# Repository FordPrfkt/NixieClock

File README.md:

# NixieClock
ESP12 based universal base board for nixie clocks and IN14-Tube board

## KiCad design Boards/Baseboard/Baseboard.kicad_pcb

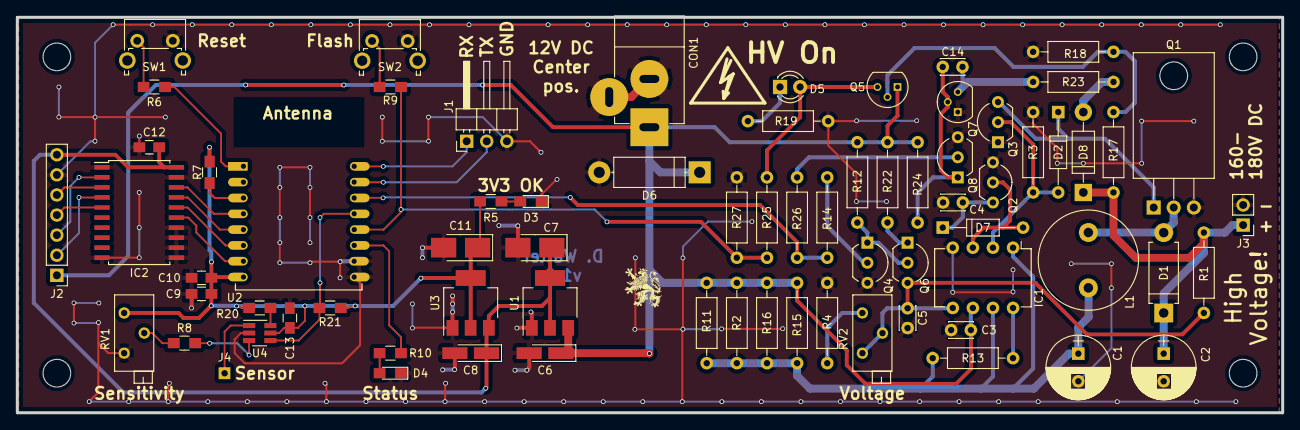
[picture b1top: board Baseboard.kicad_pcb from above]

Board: 2 copper layers, 160.0 x 50.0 mm, 73 parts (0 on the bottom side), 48 nets.

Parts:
C1: 220µF/25V; CP_Radial_D8.0mm_P3.50mm
C2: 2µ2 / 250V; CP_Radial_D8.0mm_P3.50mm
C3: 100nF; C_Disc_D3.0mm_W2.0mm_P2.50mm
C4, C14: 1.5nF; C_Disc_D3.0mm_W2.0mm_P2.50mm
C5: 10nF; C_Disc_D3.0mm_W2.0mm_P2.50mm
C6, C8: 10µF; CP_Tantalum_Case-A_EIA-3216-18_Hand
C7, C11: 100µF; CP_Tantalum_Case-B_EIA-3528-21_Hand
C9: 1µF; C_0805_HandSoldering
C10, C12, C13: 100nF; C_0805_HandSoldering
CON1: Power; JACK_ALIM
D1: MUR120; D_DO-15_P10.16mm_Horizontal
D2: 1N914; D_DO-35_SOD27_P10.16mm_Horizontal
D3: LED; LED_0805_HandSoldering
D4: Status; LED_0805_HandSoldering
D5: LED; LED_D3.0mm
D6: D_TVS; D_5W_P12.70mm_Horizontal
D7: 1N5711; D_DO-35_SOD27_P10.16mm_Horizontal
D8: ZD20 / 1W; D_DO-41_SOD81_P10.16mm_Horizontal
IC1: MC34063AP; DIP-8_W7.62mm
IC2: 74HCT245DW; SOIC-20W_7.5x12.8mm_Pitch1.27mm
J1: Serial; Pin_Header_Angled_1x03_Pitch2.54mm
J2: Display; Socket_Strip_Straight_1x07_Pitch2.54mm
J3: HV; Socket_Strip_Straight_1x02_Pitch2.54mm
J4: Sensor; Measurement_Point_Square-TH_Small
L1: 270µH / 1.2A; L_Radial_D12.5mm_P7.00mm_Fastron_09HCP
Q1: IRF740; TO-220-3_Horizontal
Q2, Q3: BC327; TO-92_Inline_Wide
Q4, Q6, Q8: BC337; TO-92_Inline_Wide
Q5: BS170; TO-92_Molded_Narrow
Q7: MPSA42; TO-92_Molded_Narrow
R1: 560k; R_Axial_DIN0207_L6.3mm_D2.5mm_P10.16mm_Horizontal
R2, R11, R15, R16: 1R37; R_Axial_DIN0207_L6.3mm_D2.5mm_P10.16mm_Horizontal
R3, R14, R22, R26: 1k; R_Axial_DIN0207_L6.3mm_D2.5mm_P10.16mm_Horizontal
R4: 3k65; R_Axial_DIN0207_L6.3mm_D2.5mm_P10.16mm_Horizontal
R5, R10: 68R; R_0805_HandSoldering
R6, R9: 470R; R_0805_HandSoldering
R7, R8, R20, R21: 10k; R_0805_HandSoldering
R12, R24: 4k7; R_Axial_DIN0207_L6.3mm_D2.5mm_P10.16mm_Horizontal
R13: 180R; R_Axial_DIN0207_L6.3mm_D2.5mm_P10.16mm_Horizontal
R17: 220k; R_Axial_DIN0207_L6.3mm_D2.5mm_P10.16mm_Horizontal
R18: 120k; R_Axial_DIN0207_L6.3mm_D2.5mm_P10.16mm_Horizontal
R19: 680R; R_Axial_DIN0207_L6.3mm_D2.5mm_P10.16mm_Horizontal
R23: 47R; R_Axial_DIN0207_L6.3mm_D2.5mm_P10.16mm_Horizontal
R25: 68k; R_Axial_DIN0207_L6.3mm_D2.5mm_P10.16mm_Horizontal
R27: 27k; R_Axial_DIN0207_L6.3mm_D2.5mm_P10.16mm_Horizontal
RV1: 100k; Potentiometer_Trimmer_Bourns_3296Z
RV2: 1kR; Potentiometer_Trimmer_Bourns_3296Z
SW1: Reset; SW_Tactile_SPST_Angled_PTS645Vx39-2LFS
SW2: Flash; SW_Tactile_SPST_Angled_PTS645Vx39-2LFS
U1: LM1117-5.0; SOT-223-3_TabPin2
U2: ESP-12
U3: LM1117-3.3; SOT-223-3_TabPin2
U4: MTCH101; SOT-23-6_Handsoldering

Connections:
+3V3: C9.1, C10.1, C11.1, C13.1, R5.1, R7.1, R20.1, R21.1, RV1.1, U2.8, U3.2, U4.5
+5V: C7.1, C8.1, C12.1, IC2.20, J2.7, U1.2, U3.3
+12V: C3.1, C6.1, CON1.1, D6.1, IC1.6, J2.1, Q5.1, R2.2, R11.2, R12.2, R15.2, R16.2, R22.2, R24.2, U1.3
/175V: C2.1, D1.1, D8.1, J3.1, R1.2, R17.2
/CLK: IC2.15, U2.7
/CS: IC2.18, U2.4
/MOSI: IC2.17, U2.5
/PWM: IC2.16, U2.6
GND: C1.2, C2.2, C3.2, C4.2, C5.2, C6.2, C7.2, C8.2, C9.2, C10.2, C11.2, C12.2, C13.2, CON1.2, CON1.3, D3.1, D4.1, D6.2, IC1.4, IC2.1, IC2.10, IC2.11, IC2.12, IC2.13, IC2.14, IC2.19, J1.3, J2.6, J3.2, Q1.3, Q2.1, Q3.1, Q4.3, Q7.1, Q8.3, R3.1, R4.1, R18.1, R19.2, R27.1, RV1.3, SW1.2, SW2.2, U1.1, U2.9, U2.10, U3.1, U4.2
HV_On: R14.2, R26.2, U2.14
HV_Status: D5.2, Q5.3, R25.2
unnamed: C1.1, IC1.1, IC1.7, L1.1, R2.1, R11.1, R13.2, R15.1, R16.1
unnamed: C4.1, D7.1, Q2.3
unnamed: C5.1, IC1.5, Q6.3, R1.1, RV2.2, RV2.3
unnamed: C14.1, Q7.3, R23.1
unnamed: C14.2, Q7.2, Q8.1, R24.1
unnamed: D1.2, L1.2, Q1.2
unnamed: D2.1, Q1.1, Q3.3
unnamed: D2.2, IC1.2, Q3.2, R3.2
unnamed: D3.2, R5.2
unnamed: D4.2, R10.2
unnamed: D5.1, R19.1
unnamed: D7.2, IC1.3, Q2.2
unnamed: D8.2, R23.2
unnamed: IC1.8, R13.1
unnamed: IC2.2, J2.3
unnamed: IC2.3, J2.5
unnamed: IC2.4, J2.2
unnamed: IC2.5, J2.4
unnamed: J1.1, U2.16
unnamed: J1.2, U2.15
unnamed: J4.1, U4.1
unnamed: Q4.1, Q6.2, R12.1
unnamed: Q4.2, R14.1
unnamed: Q5.2, R17.1, R18.2
unnamed: Q6.1, R22.1
unnamed: Q8.2, R26.1
unnamed: R4.2, RV2.1
unnamed: R6.1, U2.1
unnamed: R6.2, SW1.1
unnamed: R7.2, U2.3
unnamed: R8.1, U4.3
unnamed: R8.2, RV1.2
unnamed: R9.2, SW2.1
unnamed: R10.1, U2.11
unnamed: R20.2, U4.6
unnamed: R9.1, R25.1, R27.2, U2.12
Prx_Det: R21.2, U2.13, U4.4

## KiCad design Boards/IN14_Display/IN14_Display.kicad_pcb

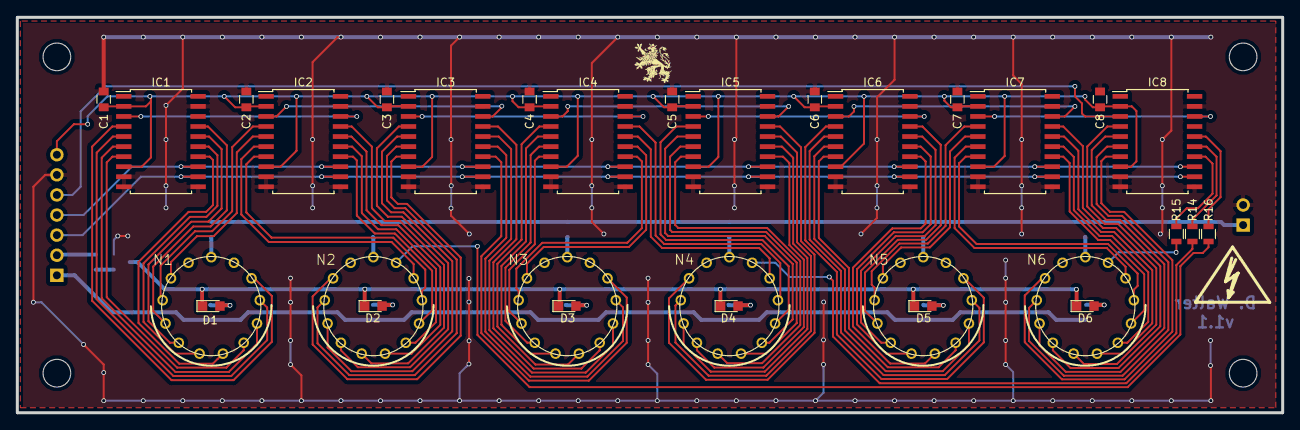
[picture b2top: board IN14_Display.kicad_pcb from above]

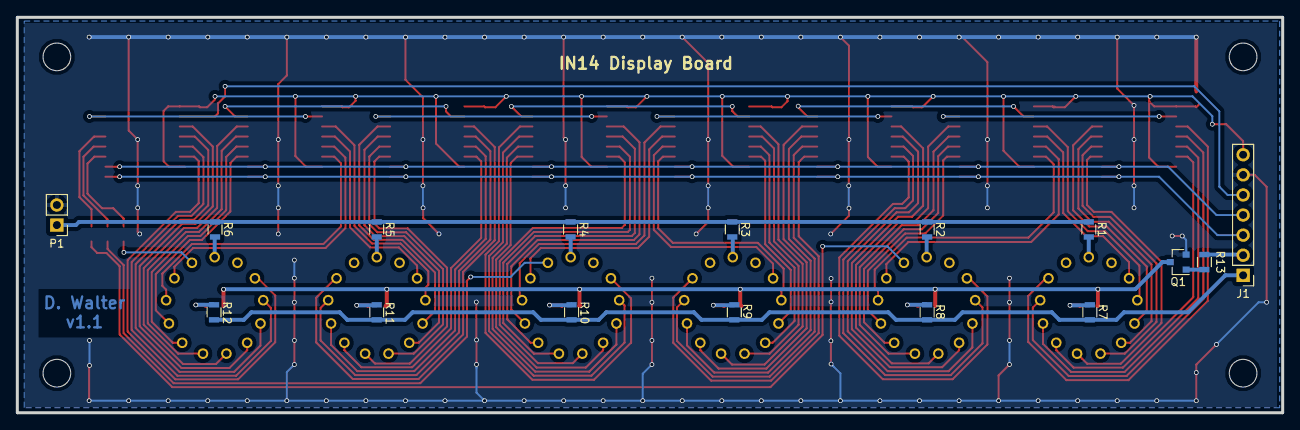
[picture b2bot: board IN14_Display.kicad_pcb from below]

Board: 2 copper layers, 160.0 x 50.0 mm, 47 parts (16 on the bottom side), 95 nets.

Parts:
C1, C2, C3, C4, C5, C6, C7, C8: 100nF; C_0805
D1, D2, D3, D4, D5, D6: LED; LED_0805
IC1, IC2, IC3, IC4, IC5, IC6, IC7, IC8: TPIC6B596DW; SOIC-20W_7.5x12.8mm_Pitch1.27mm
J1: Conn_01x07; Pin_Header_Straight_1x07_Pitch2.54mm
N1, N2, N3, N4, N5, N6: IN-14; russian-nixies-IN-14
P1: CONN_01X02; Pin_Header_Straight_1x02_Pitch2.54mm
Q1: BC817; SOT-23
R1, R2, R3, R4, R5, R6, R13: 2k2; R_0805
R7, R8, R9, R10, R11, R12: 120R; R_0805
R14, R15, R16: 16k; R_0805

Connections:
+12V: J1.1, R7.1, R8.1, R9.1, R10.1, R11.1, R12.1
GND: C1.2, C2.2, C3.2, C4.2, C5.2, C6.2, C7.2, C8.2, IC1.9, IC1.10, IC1.11, IC1.19, IC2.9, IC2.10, IC2.11, IC2.19, IC3.9, IC3.10, IC3.11, IC3.19, IC4.9, IC4.10, IC4.11, IC4.19, IC5.9, IC5.10, IC5.11, IC5.19, IC6.9, IC6.10, IC6.11, IC6.19, IC7.9, IC7.10, IC7.11, IC7.19, IC8.9, IC8.10, IC8.11, IC8.19, J1.6, P1.2, Q1.2
unnamed: D1.1, D2.1, D3.1, D4.1, D5.1, D6.1, Q1.3
unnamed: D1.2, R7.2
unnamed: D2.2, R8.2
unnamed: D3.2, R9.2
unnamed: D4.2, R10.2
unnamed: D5.2, R11.2
unnamed: D6.2, R12.2
unnamed: IC1.3, IC2.18
unnamed: IC1.4, N1.1
unnamed: IC1.5, N1.2
unnamed: IC1.6, N1.3
unnamed: IC1.7, N1.4
unnamed: IC1.12, IC2.12, IC3.12, IC4.12, IC5.12, IC6.12, IC7.12, IC8.12, J1.3
unnamed: IC1.13, IC2.13, IC3.13, IC4.13, IC5.13, IC6.13, IC7.13, IC8.13, J1.4
unnamed: IC1.14, N1.5
unnamed: IC1.15, N1.6
unnamed: IC1.16, N1.7
unnamed: IC1.17, N1.8
unnamed: IC2.3, IC3.18
unnamed: IC2.4, N1.9
unnamed: IC2.5, N1.0
unnamed: IC2.6, N2.1
unnamed: IC2.7, N2.2
unnamed: IC2.14, N2.3
unnamed: IC2.15, N2.4
unnamed: IC2.16, N2.5
unnamed: IC2.17, N2.6
unnamed: IC3.3, IC4.18
unnamed: IC3.4, N2.7
unnamed: IC3.5, N2.8
unnamed: IC3.6, N2.9
unnamed: IC3.7, N2.0
unnamed: IC3.14, N3.1
unnamed: IC3.15, N3.2
unnamed: IC3.16, N3.3
unnamed: IC3.17, N3.4
unnamed: IC4.3, IC5.18
unnamed: IC4.4, N3.5
unnamed: IC4.5, N3.6
unnamed: IC4.6, N3.7
unnamed: IC4.7, N3.8
unnamed: IC4.14, N3.9
unnamed: IC4.15, N3.0
unnamed: IC4.16, N4.1
unnamed: IC4.17, N4.2
unnamed: IC5.3, IC6.18
unnamed: IC5.4, N4.3
unnamed: IC5.5, N4.4
unnamed: IC5.6, N4.5
unnamed: IC5.7, N4.6
unnamed: IC5.14, N4.7
unnamed: IC5.15, N4.8
unnamed: IC5.16, N4.9
unnamed: IC5.17, N4.0
unnamed: IC6.3, IC7.18
unnamed: IC6.4, N5.1
unnamed: IC6.5, N5.2
unnamed: IC6.6, N5.3
unnamed: IC6.7, N5.4
unnamed: IC6.14, N5.5
unnamed: IC6.15, N5.6
unnamed: IC6.16, N5.7
unnamed: IC6.17, N5.8
unnamed: IC7.3, IC8.18
unnamed: IC7.4, N5.9
unnamed: IC7.5, N5.0
unnamed: IC7.6, N6.1
unnamed: IC7.7, N6.2
unnamed: IC7.14, N6.3
unnamed: IC7.15, N6.4
unnamed: IC7.16, N6.5
unnamed: IC7.17, N6.6
unnamed: IC8.3, J1.5
unnamed: IC8.4, N6.7
unnamed: IC8.5, N6.8
unnamed: IC8.6, N6.9
unnamed: IC8.7, N6.0
unnamed: IC8.14, R15.1
unnamed: IC8.15, R14.1
unnamed: IC8.16, R16.1
unnamed: J1.2, R13.2
unnamed: N1.A, R1.2
unnamed: N2.A, R2.2
unnamed: N2.RHDP, R16.2
unnamed: N3.A, R3.2
unnamed: N4.A, R4.2
unnamed: N4.RHDP, R14.2
unnamed: N5.A, R5.2
unnamed: N6.A, R6.2
unnamed: N6.RHDP, R15.2
unnamed: P1.1, R1.1, R2.1, R3.1, R4.1, R5.1, R6.1
unnamed: Q1.1, R13.1
VCC: C1.1, C2.1, C3.1, C4.1, C5.1, C6.1, C7.1, C8.1, IC1.2, IC1.8, IC2.2, IC2.8, IC3.2, IC3.8, IC4.2, IC4.8, IC5.2, IC5.8, IC6.2, IC6.8, IC7.2, IC7.8, IC8.2, IC8.8, J1.7

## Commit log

2018-02-18 Initial Commiz
2018-02-18 Set theme jekyll-theme-time-machine
2018-02-18 Create LICENSE
2018-02-18 Removed old schematics
2018-02-19 Layout chnages
2018-03-19 Board layout done
2018-06-23 Layout done, before PCB order
2018-12-07 Production Version, Firmware Work in Progress
2018-12-09 Update ignore list
2019-03-02 Firmware - Work in progress
2019-04-07 Webserver implementation
2019-04-27 Web Page, Work in progress
2019-04-27 Eclipse settings
